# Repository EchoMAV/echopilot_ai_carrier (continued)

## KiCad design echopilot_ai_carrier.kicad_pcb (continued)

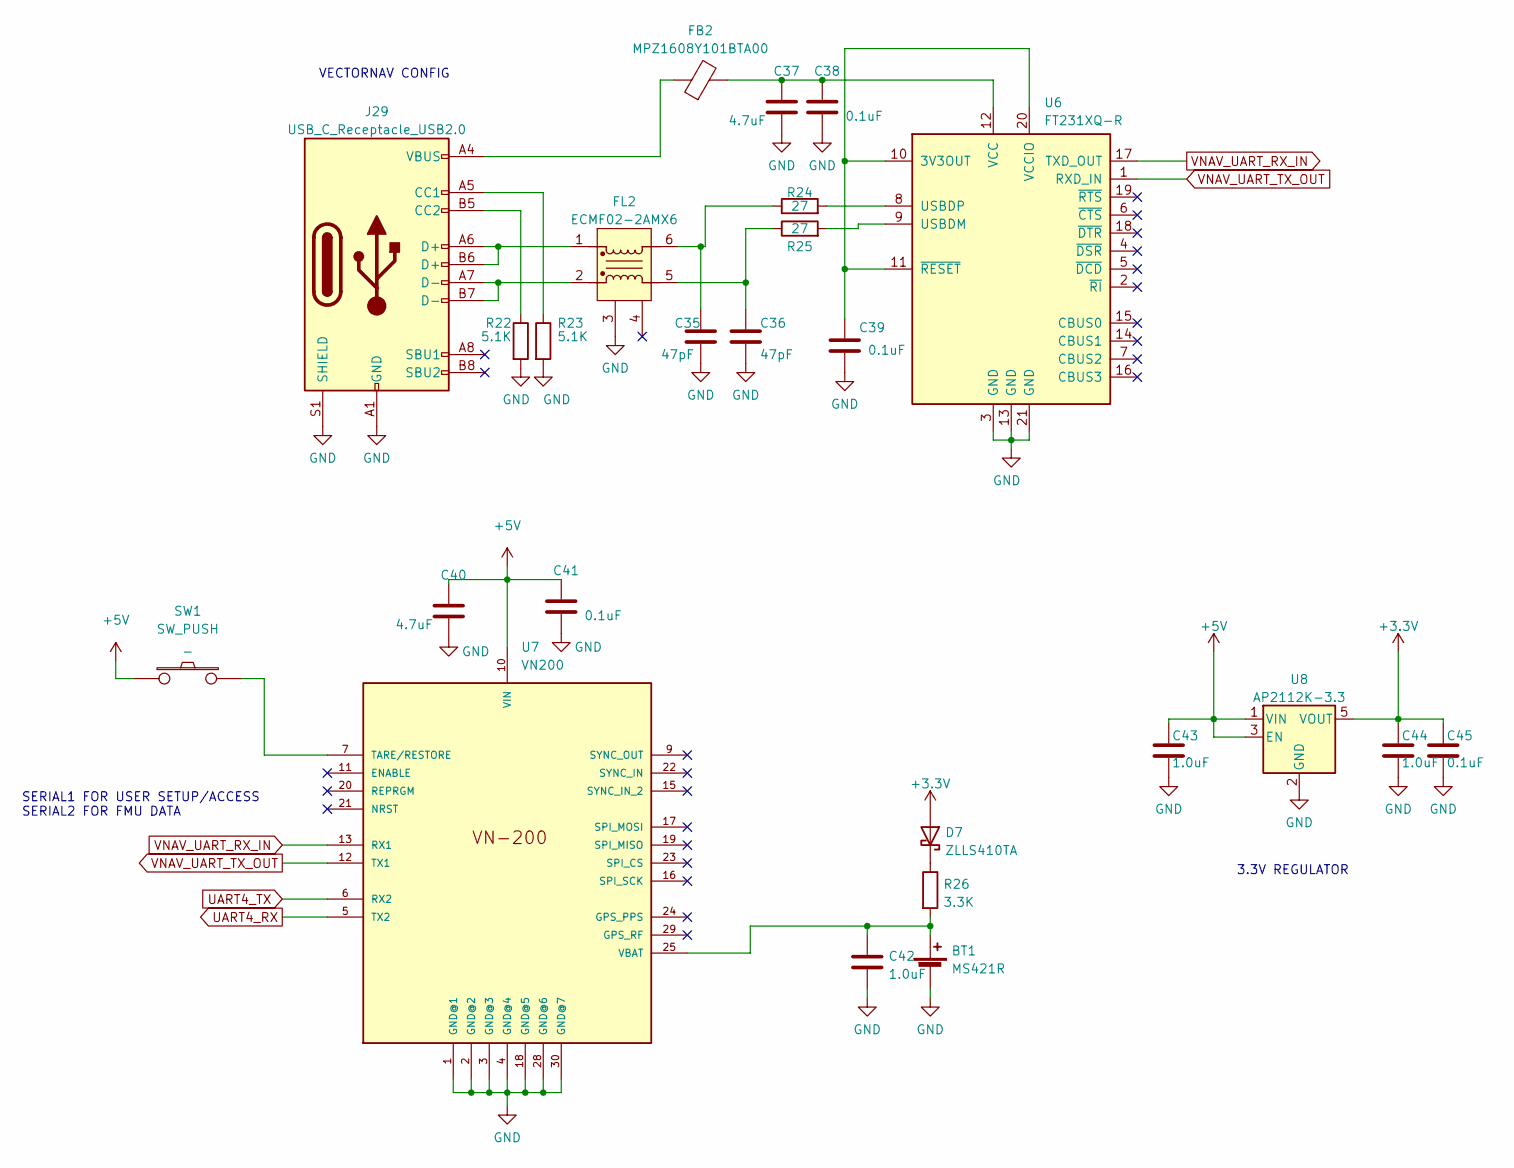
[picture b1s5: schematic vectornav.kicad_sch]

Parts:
BT1: MS421R; SEIKO_ML414H_IV01E; Part Num MS421R IV03E
C35, C36: 47pF; C_0201_0603Metric; Part Num 02013A470JAT2A
C37, C40: 4.7uF; C_0805_2012Metric; Part Num CL21B475KOFNFNE
C38, C39, C41: 0.1uF; C_0201_0603Metric; Part Num GRM033R61E104KE14J
C42, C43, C44: 1.0uF; C_0805_2012Metric; Part Num C2012X7R1E105K125AB
C45: 0.1uF; C_0402_1005Metric; Part Num CL05B104KB5NNNC
D7: ZLLS410TA; D_SOD-323; Part Num ZLLS410TA
FB2: MPZ1608Y101BTA00; L_0603_1608Metric; Part Num MPZ1608Y101BTA00
FL2: ECMF02-2AMX6; QFN-6L_STM; Part Num ECMF02-2AMX6
J29: USB_C_Receptacle_USB2.0; USB_C_Receptacle_Amphenol_12401610E4-2A; Part Num 12401610E4#2A
R22, R23: 5.1K; R_0201_0603Metric; Part Num ERJ-1GNJ512C
R24, R25: 27; R_0201_0603Metric; Part Num ERJ-1GNJ270C
R26: 3.3K; R_0402_1005Metric; Part Num ERJ-PA2F3301X
SW1: SW_PUSH; SW_B3U-1000P; Voltage _; Tolerance _; Part Num B3U-1000P
U6: FT231XQ-R; QFN20_FT231XQ_FTD; Part Num FT231XQ-R
U7: VN200; 7X8CASTLE
U8: AP2112K-3.3; SOT-23-5; Part Num AP2112K-3.3TRG1

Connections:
+3V3: C44.1, C45.1, D7.2 (A), U8.5 (VOUT)
GND: BT1.2 (-), C35.2, C36.2, C37.2, C38.2, C39.2, C40.2, C41.2, C42.2, C43.2, C44.2, C45.2, FL2.3 (GND), J29.A1 (GND), J29.A12 (GND), J29.B1 (GND), J29.B12 (GND), J29.S1 (SHIELD), R22.2, R23.2, U6.3 (GND), U6.13 (GND), U6.21 (GND), U7.1 (GND@1), U7.2 (GND@2), U7.3 (GND@3), U7.4 (GND@4), U7.18 (GND@5), U7.28 (GND@6), U7.30 (GND@7), U8.2 (GND); also elsewhere on the board
unnamed: BT1.1 (+), C42.1, R26.2, U7.25 (VBAT)
unnamed: C35.1, FL2.6 (D+_OUT), R24.1
unnamed: C36.1, FL2.5 (D-_OUT), R25.1
unnamed: C37.1, C38.1, FB2.2, U6.12 (VCC)
unnamed: C39.1, U6.10 (3V3OUT), U6.11 (~RESET), U6.20 (VCCIO)
unnamed: D7.1 (K), R26.1
unnamed: FB2.1, J29.A4 (VBUS), J29.A9 (VBUS), J29.B4 (VBUS), J29.B9 (VBUS)
unnamed: FL2.1 (D+_IN), J29.A6 (D+), J29.B6 (D+)
unnamed: FL2.2 (D-_IN), J29.A7 (D-), J29.B7 (D-)
unnamed: J29.A5 (CC1), R23.1
unnamed: J29.B5 (CC2), R22.1
unnamed: R24.2, U6.8 (USBDP)
unnamed: R25.2, U6.9 (USBDM)
unnamed: SW1.2, U7.7 (TARE/RESTORE)
UART4_RX: U7.5 (TX2); also elsewhere on the board
UART4_TX: U7.6 (RX2); also elsewhere on the board
VNAV_UART_RX_IN: U6.17 (TXD_OUT), U7.13 (RX1)
VNAV_UART_TX_OUT: U6.1 (RXD_IN), U7.12 (TX1)

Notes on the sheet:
3.3V REGULATOR
SERIAL1 FOR USER SETUP/ACCESS SERIAL2 FOR FMU DATA
VECTORNAV CONFIG

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
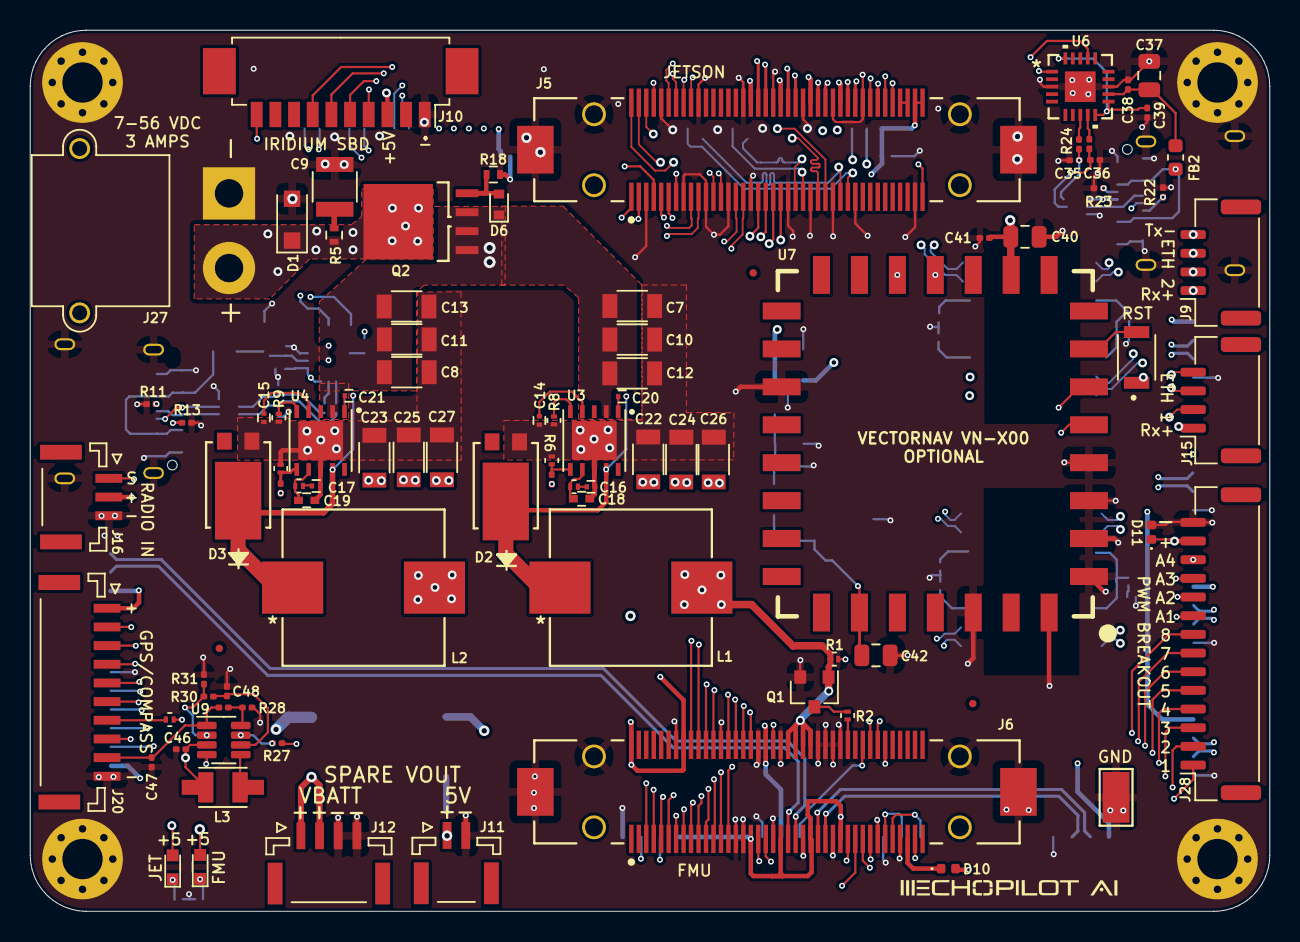
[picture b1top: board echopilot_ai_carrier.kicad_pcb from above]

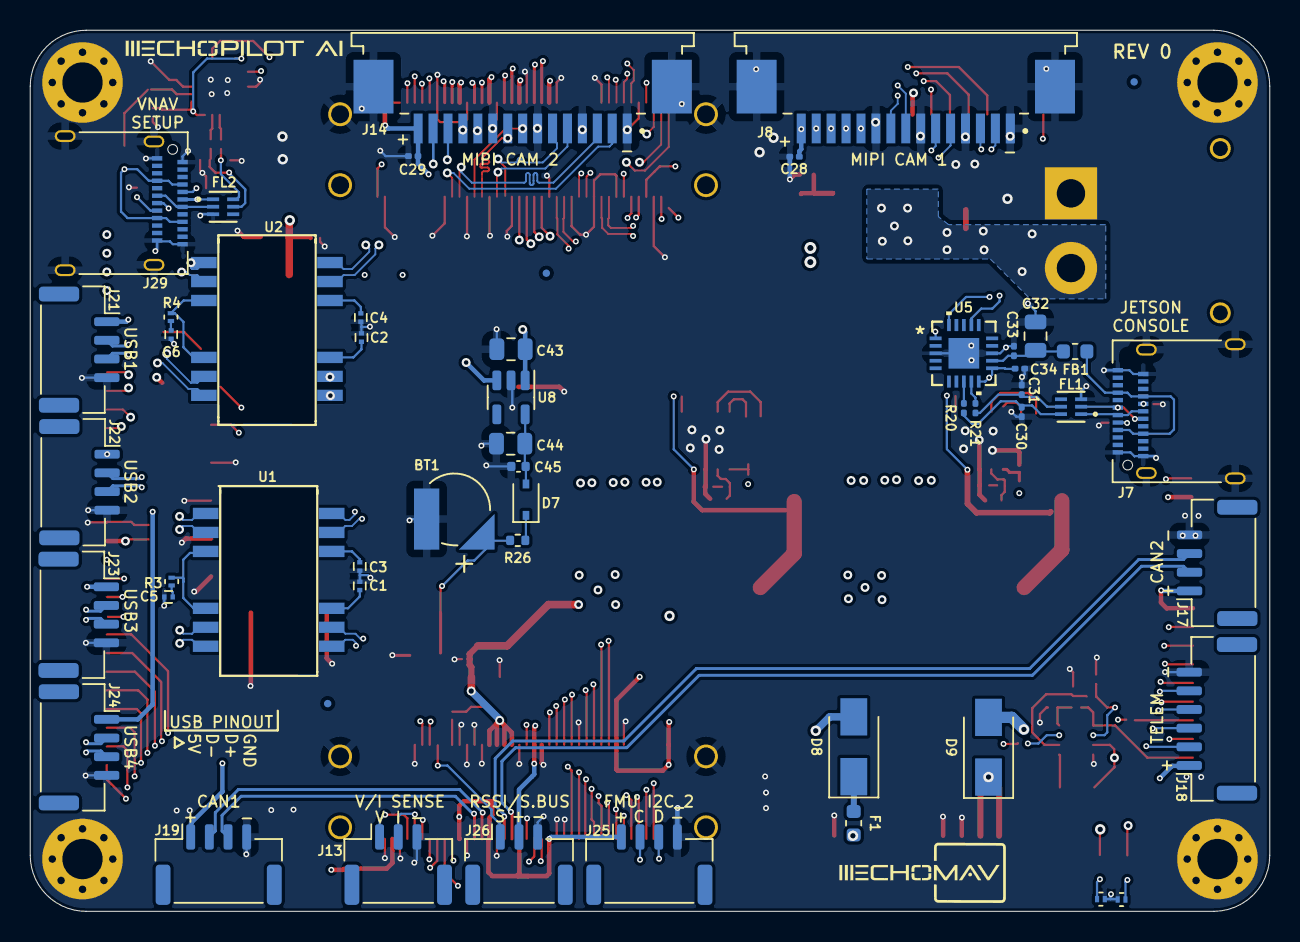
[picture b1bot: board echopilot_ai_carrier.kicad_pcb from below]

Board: 8 copper layers, 83.0 x 59.0 mm, 147 parts (52 on the bottom side), 168 nets.

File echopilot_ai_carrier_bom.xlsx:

EchoPilot AI Carrier - Public Release
Item | Qty | Reference(s) | Value | LibPart | Footprint | Part Num | Notes
1 | 1 | BT1 | MS421R | Device:Battery_Cell | UVDL:SEIKO_ML414H_IV01E | MS421R IV03E
2 | 6 | C1, C2, C3, C4, C20, C21 | 0.1uF | Device:C | Capacitors_SMD:C_0201 | GRM033R61E104KE14J
3 | 2 | C5, C6 | 1000pF | Device:C | Capacitors_SMD:C_0201 | GRM033R71H102KA12D
4 | 6 | C7, C8, C10, C11, C12, C13 | 2.2uF 100V | Device:C | Capacitors_SMD:C_1206 | 12061C225KAT2A
5 | 1 | C9 | 10uF 100V | Device:C | Capacitors_SMD:C_1210 | GRM32EC72A106KE05L
6 | 2 | C14, C15 | 10nF | Device:C | Capacitors_SMD:C_0201 | GRM033R71E103KE14D
7 | 2 | C16, C17 | 4.7nF | Device:C | Capacitors_SMD:C_0201 | GRM033R61E472KA12D
8 | 2 | C18, C19 | 47pF | Device:C | Capacitors_SMD:C_0402 | C0402C470J3RACAUTO
9 | 6 | C22, C23, C24, C25, C26, C27 | 47uF 10V | Device:C | Capacitors_SMD:C_1206 | CL31A476MPHNNNE
10 | 7 | C28, C29, C33, C34, C38, C39, C41 | 0.1uF | Device:C | Capacitor_SMD:C_0201_0603Metric | GRM033R61E104KE14J
11 | 4 | C30, C31, C35, C36 | 47pF | Device:C | Capacitor_SMD:C_0201_0603Metric | 02013A470JAT2A
12 | 3 | C32, C37, C40 | 4.7uF | Device:C | Capacitor_SMD:C_0805_2012Metric | CL21B475KOFNFNE
13 | 3 | C42, C43, C44 | 1.0uF | Device:C | Capacitor_SMD:C_0805_2012Metric | C2012X7R1E105K125AB
14 | 1 | C45 | 0.1uF | Device:C | Capacitor_SMD:C_0402_1005Metric | CL05B104KB5NNNC
15 | 1 | C46 | 1.0uF | Device:C | Capacitor_SMD:C_0201_0603Metric | CL03A105MO3NRNH
16 | 1 | C47 | 5600pF | Device:C | Capacitor_SMD:C_0201_0603Metric | GRM033R61E562KA12D
17 | 1 | C48 | 0.47uF | Device:C | Capacitor_SMD:C_0201_0603Metric | EMK063BBJ474KPLF
18 | 1 | D1 | TVS | osrf_device_fork:TVS | Diodes_SMD:D_SOD-123F | ATV02W101B-HF
19 | 2 | D2, D3 | PDS760-13 | Device:D_Schottky | UVDL:PDS760-13 | PDS760-13
20 | 2 | D4, D5 | LED_G | Device:LED | LEDs:LED_0603 | 150060VS75000
21 | 1 | D6 | D_Zener | Device:D_Zener | Diodes_SMD:D_SOD-523 | MM5Z12VT1G
22 | 1 | D7 | ZLLS410TA | Device:D_Schottky | Diode_SMD:D_SOD-323 | ZLLS410TA
23 | 2 | D8, D9 | D_Schottky | Device:D_Schottky | Diode_SMD:D_SMA | B340LA-13-F
24 | 1 | D10 | D_Schottky | Device:D_Schottky | Diode_SMD:D_0402_1005Metric | CDBQC0130L-HF
25 | 1 | D11 | Part Num | Diode:1.5KExxA | Diode_SMD:D_0402_1005Metric | PESD0402-140
26 | 1 | F1 | 0603L100SLYR | Device:Polyfuse | Fuse:Fuse_0603_1608Metric | 0603L100SLYR
27 | 2 | FB1, FB2 | MPZ1608Y101BTA00 | Device:FerriteBead | Inductor_SMD:L_0603_1608Metric | MPZ1608Y101BTA00
28 | 2 | FL1, FL2 | ECMF02-2AMX6 | archangel:ECMF02 | UVDL:QFN-6L_STM | ECMF02-2AMX6
29 | 2 | J5, J6 | FX23L-80P-0.5SV8 | fx23l-80p-0.5sv8:FX23L-80P-0.5SV8 | UVDL:Hirose-FX23L-80P-0.5SV8-MFG | FX23L-80P-0.5SV8 | optional, increase to 10mm gap between boards to provide additional clearance, 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
30 | 2 | J7, J29 | USB_C_Receptacle_USB2.0 | Connector:USB_C_Receptacle_USB2.0 | Connector_USB:USB_C_Receptacle_Amphenol_12401610E4-2A | 12401610E4#2A
31 | 1 | J8 | 1-84952-5 | :Conn_01x15_1 | UVDL:TE_1-84952-5 | 1-84952-5
32 | 9 | J9, J15, J17, J19, J21, J22, J23, J24, J25 | Conn_01x04 | Connector_Generic:Conn_01x04 | Connector_JST:JST_GH_SM04B-GHS-TB_1x04-1MP_P1.25mm_Horizontal | SM04B-GHS-TB(LF)(SN)
33 | 1 | J10 | 532617010 | Connector_Generic:Conn_01x10 | Connectors_Molex:Molex_PicoBlade_53261-1071_10x1.25mm_Angled | 532617010
34 | 1 | J11 | Conn_01x02 | Connector_Generic:Conn_01x02 | Connectors_JST:JST_GH_SM02B-GHS-TB_02x1.25mm_Angled | SM02B-GHS-TB(LF)(SN)
35 | 1 | J12 | Conn_01x04 | Connector_Generic:Conn_01x04 | Connectors_JST:JST_GH_SM04B-GHS-TB_04x1.25mm_Angled | SM04B-GHS-TB(LF)(SN)
36 | 2 | J13, J26 | Conn_01x03 | Connector_Generic:Conn_01x03 | Connector_JST:JST_GH_SM03B-GHS-TB_1x03-1MP_P1.25mm_Horizontal | SM03B-GHS-TB(LF)(SN)
37 | 1 | J14 | 1-84952-5 | Connector_Generic:Conn_01x15 | UVDL:TE_1-84952-5 | 1-84952-5
38 | 1 | J16 | Conn_01x03 | Connector_Generic:Conn_01x03 | Connectors_JST:JST_GH_SM03B-GHS-TB_03x1.25mm_Angled | SM03B-GHS-TB(LF)(SN)
39 | 1 | J18 | Conn_01x06 | Connector_Generic:Conn_01x06 | Connector_JST:JST_GH_SM06B-GHS-TB_1x06-1MP_P1.25mm_Horizontal | SM06B-GHS-TB(LF)(SN)
40 | 1 | J20 | Conn_01x10 | Connector_Generic:Conn_01x10 | Connectors_JST:JST_GH_SM10B-GHS-TB_10x1.25mm_Angled | SM10B-GHS-TB(LF)(SN)
41 | 1 | J27 | XT30PW-M | Connector_Generic:Conn_01x02 | UVDL:AMASS_XT30PW-M_1x02_P2.50mm_Horizontal | XT30PW-M
42 | 1 | J28 | Conn_01x14 | Connector_Generic:Conn_01x14 | Connector_JST:JST_GH_SM14B-GHS-TB_1x14-1MP_P1.25mm_Horizontal | SM14B-GHS-TB(LF)(SN)-
43 | 2 | L1, L2 | ASPIAIG-F1040-7R3M-T | Device:L | UVDL:ASPIAIG-F1040-7R3M-T | ASPIAIG-F1040-7R3M-T
44 | 1 | L3 | 47uH | Device:L | UVDL:IND_LQH32CN470K23L | LQH32CN470K23L
45 | 1 | Q1 | Q_NMOS_GSD | Device:Q_NMOS_GSD | TO_SOT_Packages_SMD:SOT-23 | BSS214NH6327XTSA1
46 | 1 | Q2 | SQJ463EP-T1_GE3 | 2023-02-23_20-09-27:SQJ463EP-T1_GE3 | UVDL:TO_63EP-T1_GE3_VIS | SQJ463EP-T1_GE3
47 | 2 | R1, R28 | 10K | Device:R | Resistor_SMD:R_0201_0603Metric | ERJ-1GNF1002C
48 | 1 | R2 | 220 | Device:R | Resistor_SMD:R_0201_0603Metric | ERJ-1GNF2200C
49 | 2 | R3, R4 | 75 | Device:R | Resistor_SMD:R_0201_0603Metric | ERJ-1GNF75R0C
50 | 1 | R5 | 750m | Device:R | Resistors_SMD:R_0402 | ERJ-2BQJR75X
51 | 2 | R6, R7 | 16.9K | Device:R | Resistor_SMD:R_0201_0603Metric | ERJ-1GNF1692C
52 | 2 | R8, R9 | 243K | Device:R | Resistor_SMD:R_0201_0603Metric | ERJ-1GNF2433C
53 | 1 | R14 | 56.0K | Device:R | Resistor_SMD:R_0201_0603Metric | RC0201FR-0756KL
54 | 1 | R10 | 57.6K | Device:R | Resistor_SMD:R_0201_0603Metric | RC0201FR-0757K6L
55 | 4 | R11, R13, R22, R23 | 5.1K | Device:R | Resistor_SMD:R_0201_0603Metric | ERJ-1GNJ512C
56 | 2 | R12, R15 | 10.2K | Device:R | Resistor_SMD:R_0201_0603Metric | ERJ-1GNF1022C
57 | 2 | R16, R17 | 1.0K | Device:R | Resistor_SMD:R_0201_0603Metric | ERJ-1GEF1001C
58 | 1 | R18 | 10K | Device:R | Resistors_SMD:R_0402 | ERJ-PA2J103X
59 | 1 | R19 | 100 | Device:R | Resistor_SMD:R_0201_0603Metric | ERJ-U01F1000C
60 | 4 | R20, R21, R24, R25 | 27 | Device:R | Resistor_SMD:R_0201_0603Metric | ERJ-1GNJ270C
61 | 1 | R26 | 3.3K | Device:R | Resistor_SMD:R_0402_1005Metric | ERJ-PA2F3301X
62 | 1 | R27 | 9.09K | Device:R | Resistor_SMD:R_0201_0603Metric | ERJ-1GNF9091C
63 | 1 | R29 | 100K | Device:R | Resistor_SMD:R_0201_0603Metric | ERJ-1GEF1003C
64 | 1 | R30 | 453K | Device:R | Resistor_SMD:R_0201_0603Metric | ERJ-1GNF4533C
65 | 1 | R31 | 16.5K | Device:R | Resistor_SMD:R_0201_0603Metric | ERJ-1GNF1652C
66 | 1 | SW1 | SW_PUSH | osrf_device_fork:SW_PUSH | UVDL:SW_B3U-1000P | B3U-1000P
67 | 1 | TP1 | TestPoint | Connector:TestPoint | Measurement_Points:Test_Point_Keystone_5015_Micro-Minature | 5015 | Mfg: Keystone
68 | 2 | U1, U2 | HX0068ANLT | Microhard:HX0068ANLT | Nightcrawler:HX0068ANLT_r2 | HX0068ANLT
69 | 2 | U3, U4 | TPS54561QDPRRQ1 | TPS54561DPRR:TPS54561DPRR | UVDL:SON80P400X400X80-11N | TPS54561QDPRRQ1
70 | 2 | U5, U6 | FT231XQ-R | archangel:FT231XQ | UVDL:QFN20_FT231XQ_FTD | FT231XQ-R
71 | 1 | U7 | VN200 | VN200:VN200 | UVDL:7X8CASTLE | DNI | DNI - Optional installation of VectorNAV INS VN-X00
72 | 1 | U8 | AP2112K-3.3 | Regulator_Linear:AP2112K-3.3 | Package_TO_SOT_SMD:SOT-23-5 | AP2112K-3.3TRG1
73 | 1 | U9 | LT3469 | cube_base:LT3469 | Package_TO_SOT_SMD:SOT-23-8 | LT3469ETS8#TRMPBF

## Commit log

2023-05-04 initial
2023-05-04 cleanup
2023-09-14 cleanup ref to pixc4
2023-09-14 cleanup pdf
2023-09-14 change vectornav schematic naming for clarity
2024-01-25 updates for Rev1B boards, pinout changes on J5 and J8
2024-02-09 update to Rev1C, reverse MIPI 22 pin connector
